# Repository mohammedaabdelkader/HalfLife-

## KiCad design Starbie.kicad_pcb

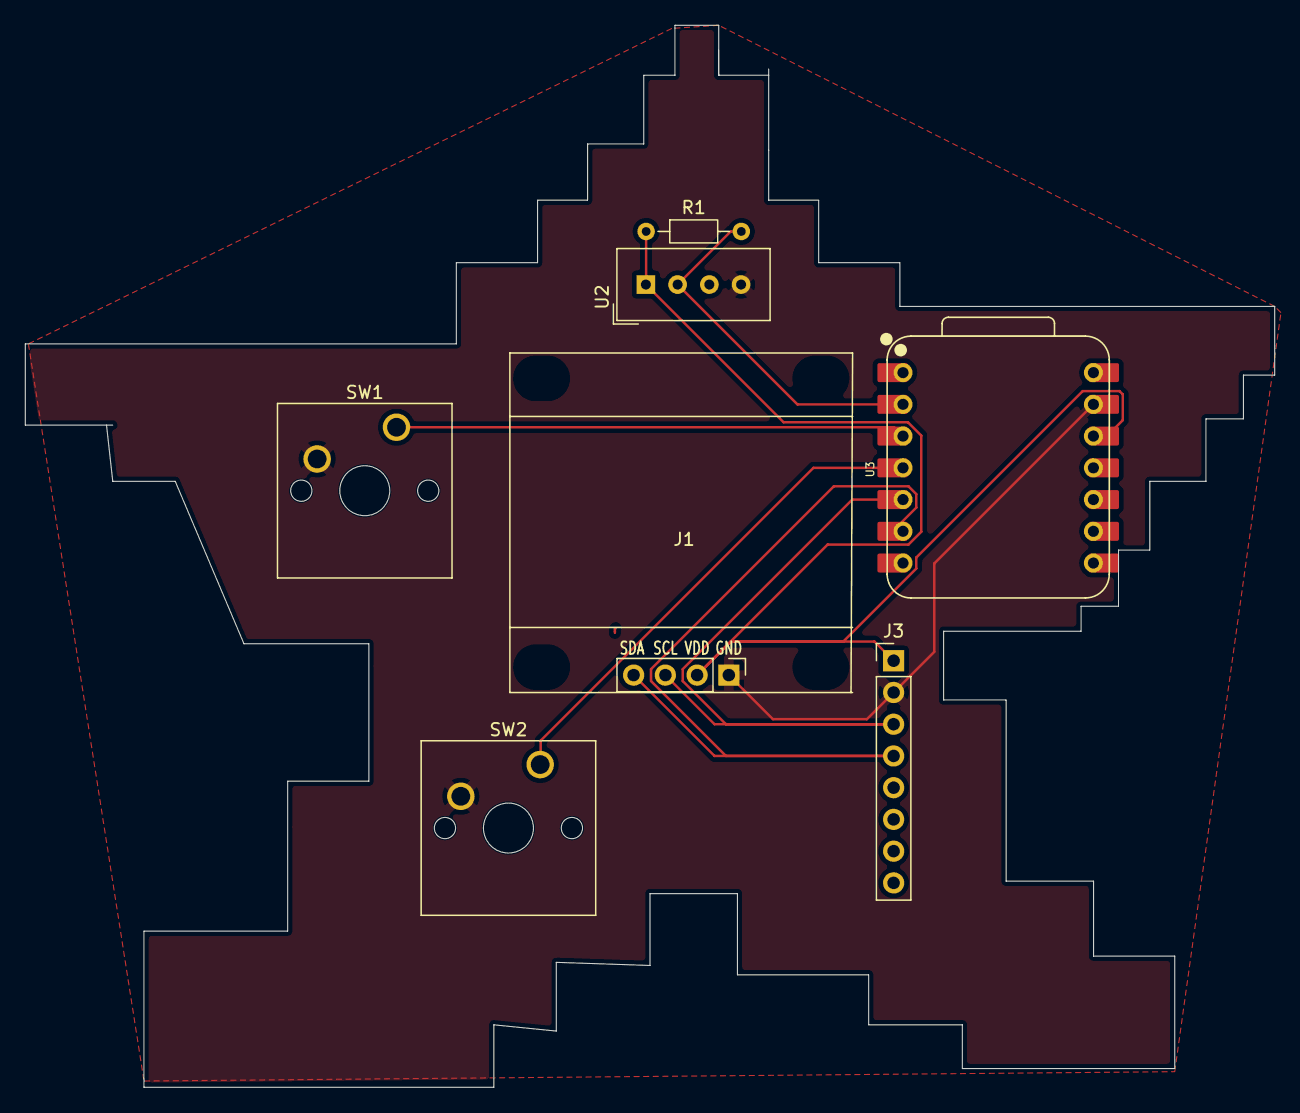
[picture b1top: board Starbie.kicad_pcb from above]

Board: 2 copper layers, 100.0 x 85.0 mm, 7 parts (0 on the bottom side), 7 nets.

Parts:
J1: SSD1306 OLED Display; Display_128x64_096_I2C
J3: Conn_01x08_Pin; PinHeader_1x08_P2.54mm_Vertical
R1: R; R_Axial_DIN0204_L3.6mm_D1.6mm_P7.62mm_Horizontal
SW1, SW2: SW_Push; SW_Cherry_MX_1.00u_PCB
U2: DHT11; Aosong_DHT11_5.5x12.0_P2.54mm
U3: XIAO-ESP32-C3-SMD; XIAO-ESP32-C6-DIP

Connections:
+3.3V: J1.2, J3.1, R1.1, U2.1 (VDD), U3.12 (3V3_OUT)
/DHT 11 Data: R1.2, U2.2 (DATA), U3.2 (D1)
/GPIO2: SW1.1, U3.3 (D2)
/GPIO3: SW2.1, U3.4 (D3)
/SCL: J1.3, J3.3, U3.5 (D4)
/SDA: J1.4, J3.4, U3.6 (D5)
GND: J1.1, J3.2, SW1.2, SW2.2, U2.4 (GND), U3.13 (GND)
